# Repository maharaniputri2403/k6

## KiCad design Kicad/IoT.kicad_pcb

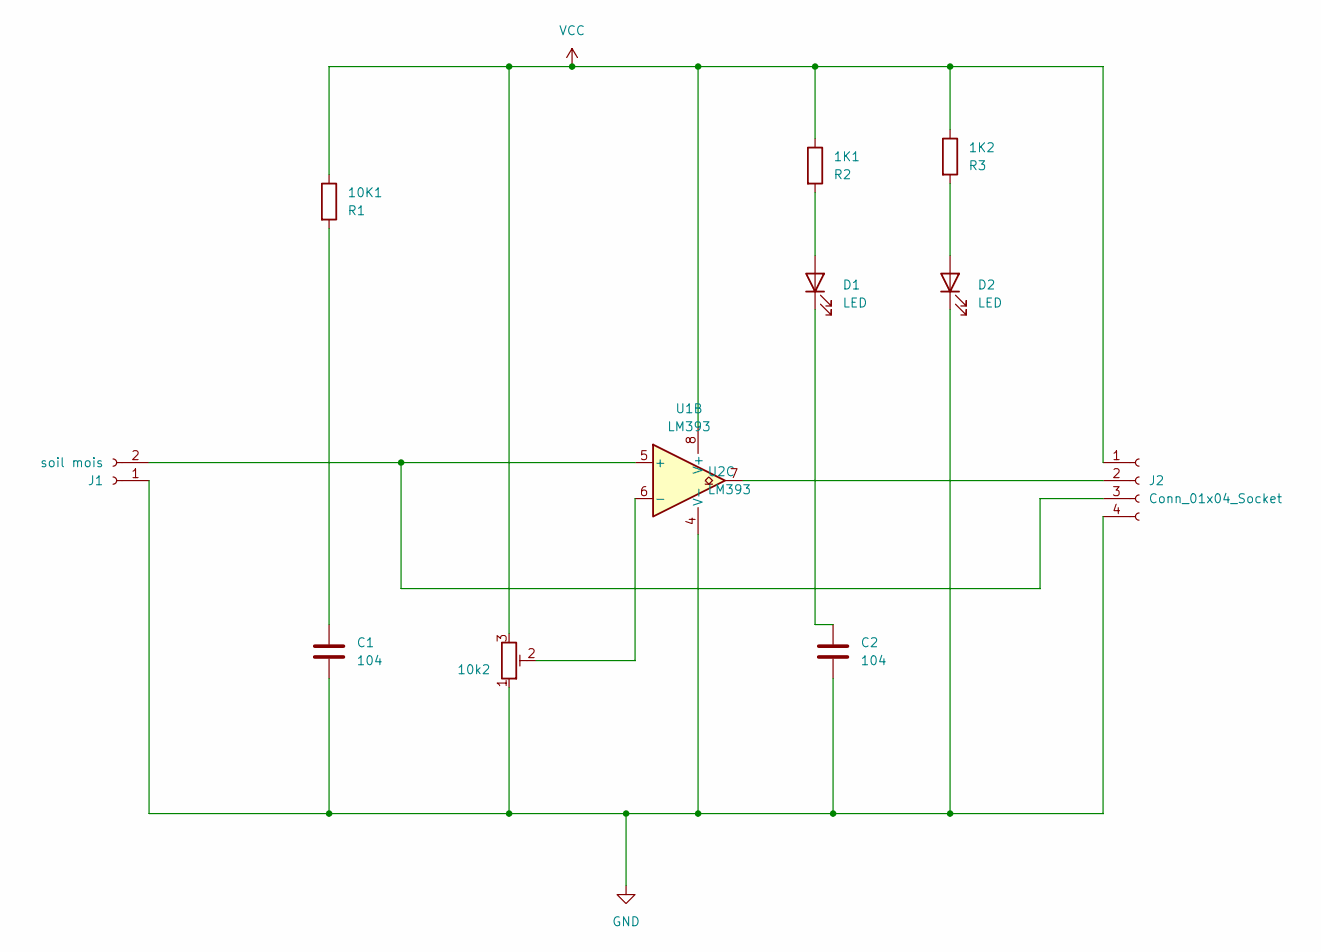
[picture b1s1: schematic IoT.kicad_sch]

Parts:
1K1: R2; R_Axial_DIN0204_L3.6mm_D1.6mm_P2.54mm_Vertical
1K2: R3; R_Axial_DIN0204_L3.6mm_D1.6mm_P2.54mm_Vertical
10K1: R1; R_Axial_DIN0204_L3.6mm_D1.6mm_P2.54mm_Vertical
10k2: R_Potentiometer_Trim; Potentiometer_Bourns_3339P_Vertical_HandSoldering
C1, C2: 104; C_Axial_L22.0mm_D10.5mm_P27.50mm_Horizontal
D1, D2: LED; LED_D3.0mm_Clear
J1: soil mois; PhoenixContact_GMSTBVA_2,5_2-G-7,62_1x02_P7.62mm_Vertical
J2: Conn_01x04_Socket; PhoenixContact_GMSTBVA_2,5_4-G-7,62_1x04_P7.62mm_Vertical
U1, U2: LM393; DIP-8_W7.62mm_Socket

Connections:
GND: 10k2.1, C1.2, C2.2, D2.1 (K), J1.1, J2.4, U2.4 (V-)
unnamed: 10K1.2, C1.1
unnamed: 1K1.2, D1.2 (A)
unnamed: C2.1, D1.1 (K)
unnamed: 1K2.2, D2.2 (A)
unnamed: J1.2, J2.3, U1.5 (+)
unnamed: J2.2, U1.7
unnamed: 10k2.2, U1.6 (-)
VCC: 1K1.1, 1K2.1, 10K1.1, 10k2.3, J2.1, U2.8 (V+)

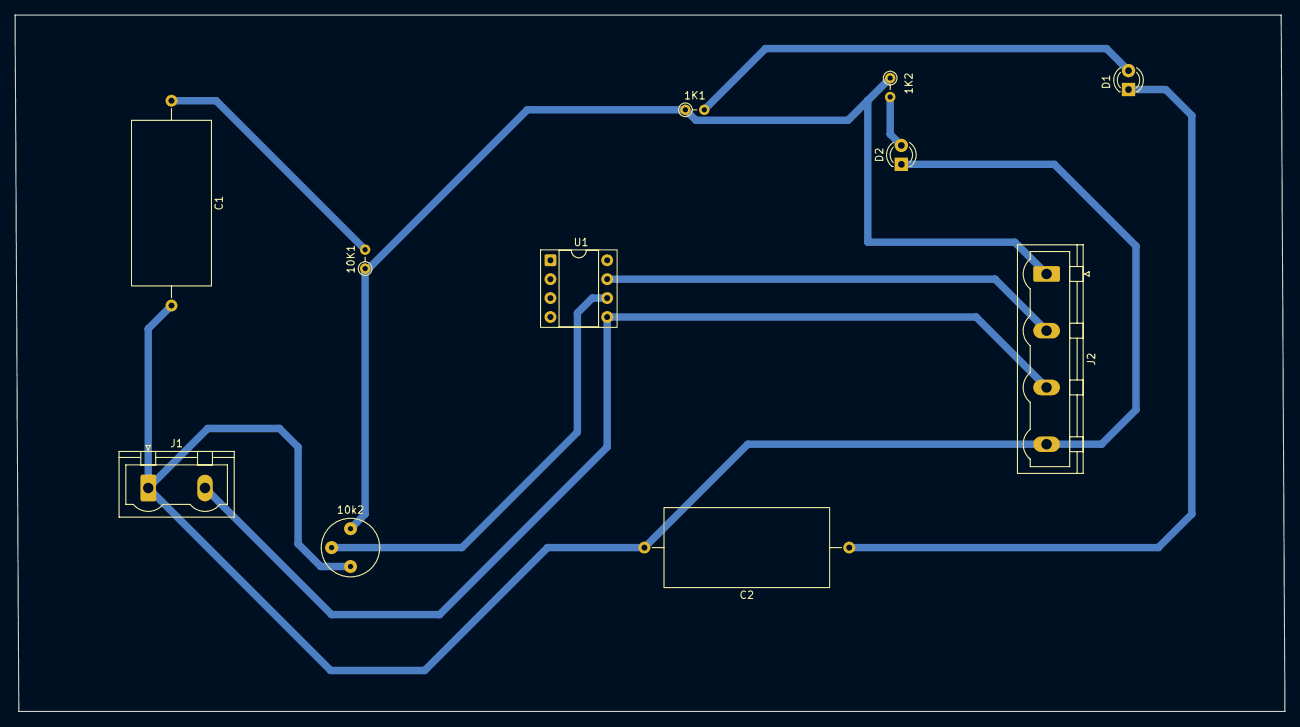
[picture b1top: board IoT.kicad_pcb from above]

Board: 2 copper layers, 170.5 x 93.5 mm, 11 parts (0 on the bottom side), 9 nets.
